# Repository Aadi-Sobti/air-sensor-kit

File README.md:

# ProseFire community air sensor kit

_"ProseFire" is a placeholder name._

A low-cost PM2.5 sensor kit that anyone can build and set up in minutes: a NodeMCU (ESP8266) board plus a
Plantower PMS5003 sensor, a small backend, and a public air-quality map.

## What's where
| Path | What it's for |
|---|---|
| `firmware/` | Sensor firmware (PlatformIO, ESP8266) |
| `backend/` | Firebase functions, database rules, emulator tests |
| `web/` | Website: setup page, owner page, public map |
| `tools/` | Serial log capture, release-build check, (later) device simulator and factory provisioning |
| `docs/PLAN.md` | Milestones and progress |
| `docs/decisions.md` | What's decided and what's still open |
| `docs/USER_FLOW.md` | Exactly what kit recipients and volunteers do |
| `docs/FUTURE.md` | Fire Watch + outage plans (later phases) |
| `docs/reference/` | The original O2NYC workshop deck (old wiring, for reference only) |

## Developer setup (macOS)
```bash
brew install platformio firebase-cli node@22 python@3.12
python3.12 -m venv tools/.venv && tools/.venv/bin/pip install -r tools/requirements.txt
export PATH="$(brew --prefix node@22)/bin:$PATH"   # backend + web use Node 22
```

## Checks (same as CI)
```bash
pio run -d firmware -e release -e dev && pio test -d firmware -e native && python3 tools/check_release.py
tools/.venv/bin/python -m pytest -q tools/tests
(cd backend && npm --prefix functions ci && npm --prefix functions run build && firebase emulators:exec --only functions,firestore "npm --prefix functions test")
(cd web && npm ci && npm test && npm run build)
```

## License
Not chosen yet. Until a license is added, this code is visible but not licensed for reuse.

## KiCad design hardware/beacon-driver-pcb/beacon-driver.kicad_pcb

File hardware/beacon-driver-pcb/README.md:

# Help-First beacon driver board (custom PCB, spin 1)

A 70 × 50 mm, 2-layer board that replaces the hand-soldered 5 × 7 cm "driver board" in the Help-First case
(`hardware/beacon-help-first/`), in the same pocket. **Status: drawn, routed and checked in KiCad 10; not ordered,
not built.** The bench units stay on perfboard with the same circuit (decision #44).

What it does, how and why: [DESIGN.md](DESIGN.md). The decisions behind it: #42–#49 in `docs/decisions.md`.

## Files
| File | What |
|---|---|
| `design.json` | **The source of truth:** every part (KiCad symbol and footprint, LCSC number, value), its pin-to-net map, and its position on the board |
| `build.py` | Turns `design.json` into the KiCad project, routes it, runs KiCad's checks and writes the JLCPCB files and pictures |
| `kigen.py`, `route.py` | Helpers: the label-style schematic writer and a small grid router (pure Python) |
| `beacon-driver.kicad_pro` / `.kicad_sch` / `.kicad_pcb` | The KiCad 10 project (generated: change `design.json` or `build.py`, not these) |
| `beacon-driver.kicad_dru` | JLCPCB-safe design rules (0.2 mm clearance and track, 0.3/0.6 mm vias, 0.5 mm copper to edge) |
| `beacon.pretty/` | Two project footprints: the Pololu U3V40F12 and the Adafruit MAX98357A breakout on their headers, with each module board's outline as the courtyard |
| `beacon-driver-schematic.pdf` | The schematic, for review |
| `beacon-driver-assembly.pdf` | Assembly drawing: every part's reference and outline (for checking JLCPCB's placement preview and naming the test points with no room on the silkscreen) |
| `jlcpcb/beacon-driver-gerbers.zip` | Gerbers + drill files to upload to JLCPCB |
| `jlcpcb/beacon-driver-bom.csv`, `jlcpcb/beacon-driver-cpl.csv` | Parts list and placement file for JLCPCB assembly (48 parts on the top side) |
| `pictures/board-top.png`, `board-bottom.png` | Renders |

## Checks (2026-11-27, KiCad 10.0.8)
- **ERC** (schematic electrical rules): 0 violations.
- **DRC** (layout rules, with schematic parity and zones refilled): 0 errors, 0 warnings, 0 unconnected pads, 0
  schematic-parity issues. Text is at least 1.0 mm high with a 0.16 mm stroke (JLCPCB's minimums).
- **Drill check:** `build.py` confirms all 192 plated holes in the drill file land on a copper pad or via in the
  Gerbers (an earlier version had the drill file on a different origin; the review caught it). Silk near the board edge is the only check turned off: the connectors overhang the right edge
  on purpose, and JLCPCB clips silk there.
- **Fit in the case:** `hardware/beacon-help-first/make_case.py` models the board, its 15 mm part height (13 mm in the
  top 17 mm strip, behind the siren holder), the battery plug and the ribbon socket on the right edge, and passes.
- **Not checked by software:** how the board behaves. That's the bench tests in DESIGN.md, run on the perfboard units
  **before ordering**.

## Rebuilding
KiCad 10.0.x must be available (its normal install needs your Mac password: `brew install --cask kicad`). Then:
```
KICAD_APP=/Applications/KiCad/KiCad.app \
  /Applications/KiCad/KiCad.app/Contents/Frameworks/Python.framework/Versions/Current/bin/python3 \
  hardware/beacon-driver-pcb/build.py
```
It prints the ERC and DRC results and exits non-zero if either finds a problem. To look at or edit the board by hand,
open `beacon-driver.kicad_pro` in KiCad (hand edits are overwritten by the next `build.py` run).

## What you need with this board (per beacon; checked 2026-11-27)
JLCPCB fits all the small parts and the four connectors. Everything else plugs in or solders on by hand. No crimping
tool is needed: the two harnesses come pre-assembled.

| Goes into | What to buy | Price | Per beacon | For 5 | Notes |
|---|---|---|---|---|---|
| **U1** | Pololu [U3V40F12](https://www.pololu.com/product/4016) 12 V booster (#42) | $9.95, $9.15 each for 5 | 1 | 5 | Header strip included. Solder it **flat** on its straight header, parts up, matching the silk (OUT GND GND VIN VIN EN). Pololu showed "backorders allowed" with no count: check stock |
| **U2** | Adafruit [3006](https://www.adafruit.com/product/3006) MAX98357A amplifier | $5.95 | 1 | 5 | Header included; the speaker terminal comes soldered on. Break the header to 7 pins. **Screw the speaker wires in before soldering U2 down** |
| U2's terminal | The speaker you already have (Adafruit [3351](https://www.adafruit.com/product/3351)) | (on the list) | 1 | 5 | Cut off its JST plug (so it can never go into J1 or the LilyGO's SOLAR socket), shorten to about 150 mm, screw in |
| **J1** | The battery (Adafruit [5035](https://www.adafruit.com/product/5035)) plugs straight in | (on the list) | 1 | 5 | Keyed. **First time only:** Hold a bare JST S2B-PH-K-S as it sits on a board (its PCB pins pointing down, the opening facing you), plug the pack in and meter the two pins underneath: the LEFT pin is pin 1 and must read + (3.6–4.2 V). If it reads −, stop and don't plug that pack into a beacon |
| **J2** | 22 AWG stranded wire, red + black: SparkFun [PRT-08865](https://www.sparkfun.com/products/8865) and [PRT-08867](https://www.sparkfun.com/products/8867) (25 ft each) | $5.95 each | ≈ 150 mm each | 1 spool each | Red from J2 "+" to the LilyGO 18650 holder's + tab (ESP32 end), black from "−" to its − tab (antenna end). Solder the holder end before the LilyGO goes on its posts |
| **J3** | A 14-pin (2 × 7) IDC ribbon cable, cut in half: 3M [M3AAA-1418J](https://www.digikey.com/en/products/detail/3m/M3AAA-1418J/229962), 1.5 ft | ≈ $5.60–6.38 (not confirmed) | ½ cable | 3 cables | **DigiKey stock not confirmed** (it blocked the check): look in a browser. Each half is about 220 mm. Peel the cut end once, between wires 7 and 8: wires 1–7 go to LilyGO row P1, 8–14 to row P2 (table in DESIGN.md). Hot-glue the ribbon near the LilyGO so the solder joints don't flex. **If it's out of stock:** 3M 89114-0001 IDC sockets (Master Electronics, $1.19 each, minimum 25) on 14-way 1.27 mm ribbon, pressed shut in a bench vise |
| **J4** | Adafruit [4876](https://www.adafruit.com/product/4876) 6-pin JST-XH-compatible cable pair | $1.25 | 1 (socket half) | 5 | Pre-crimped, 26 AWG, about 20 cm. Tag each wire with its pin number. Solder the far ends: 1–2 siren +/−, 3–4 light strip +/−, 5–6 red-button light +/− |
| **J5** | Adafruit [5090](https://www.adafruit.com/product/5090) 6-pin JST-PH-compatible cable pair | $0.95 | 1 (socket half) | 5 | Pre-crimped, 26 AWG. Pin 1 GND (daisy-chain to the green LED −, green switch, red switch and silence button with short black jumpers), 2 green LED +, 3 green switch, 4 red switch, 5 silence button; cut pin 6 short and insulate it |
| J5 pin 5 | Adafruit [1502](https://www.adafruit.com/product/1502) 16 mm yellow push button: the **SILENCE** button (#48) | $0.95 | 1 | 5 (+1 spare) | Normally open. Mounts on top of the case. Solder two wires: one to J5 pin 5, one to GND |
| **J6** | 26 AWG silicone wire, gray (tip) + black (sleeve): Adafruit [1884](https://www.adafruit.com/product/1884) and [1881](https://www.adafruit.com/product/1881), 2 m each | $0.95 each | ≈ 200 mm each | 1 gray + 2 black | Gray from "TIP" to the jack's tip lug, black from "SLV" to its sleeve lug. The extra black is for the J5 ground jumpers. Measure the shaker's plug first: it must be tip-positive (#47) |
| Under the board | Foam tape **no thicker than 1 mm** (Adafruit [5019](https://www.adafruit.com/product/5019) says both "1mm" and 0.063 in, so measure it) | $0.75 | 2 strips | 4 packs | Cut strips about 1.5 mm wide for the two ledges. Thicker tape pushes the board into the siren holder's space |
| Building | Lead-free solder (SparkFun [TOL-09163](https://www.sparkfun.com/products/9163)), heat-shrink (Adafruit [1649](https://www.adafruit.com/product/1649)), a flux pen and desoldering braid | $4.95 each | | | Tools: soldering iron, flush cutters (trim every lead under the board to 2 mm or less), wire stripper, multimeter, small screwdriver, heat gun |

**Add-on cost per beacon:** about $22 (the two modules $15.10, cables and wire about $5, the silence button $0.95),
plus the board itself. The modules and speaker are needed on perfboard too.

## Ordering from JLCPCB (founder steps; nothing has been ordered)
1. **Before ordering:** the perfboard bench units pass the bench tests in DESIGN.md, and an experienced engineer has
   looked over the schematic PDF and the board (`docs/BEACON_PCB.md` step 6).
2. **Account:** JLCPCB needs an account. Under 18, its terms need a parent's or guardian's permission, or an adult
   officer of the nonprofit can order. Payment is yours.
3. **Board:** upload `jlcpcb/beacon-driver-gerbers.zip`. Settings: 2 layers, 70 × 50 mm, 1.6 mm, 1 oz copper,
   lead-free HASL, quantity 5.
4. **Assembly:** turn on PCB Assembly, **Economic**, top side, 5 boards. Upload `beacon-driver-bom.csv` and
   `beacon-driver-cpl.csv`. Tick **"Confirm parts placement"**.
5. **Check the placement preview** against `beacon-driver-assembly.pdf`. KiCad and JLCPCB sometimes disagree on a
   part's rotation; fix any that look turned in JLCPCB's own tool. What correct looks like (board seen from the top,
   battery socket at the bottom right):
   - **C1** (the round can): + on the LEFT, the dark stripe (−) on the RIGHT.
   - **D2 and TVS1:** cathode band on the LEFT. **D1:** cathode band on the RIGHT.
   - **Q11** (square, bottom right): its 4 small pins on the LEFT, the big tab on the RIGHT toward R1.
   - **Q16** (square, left): small pins on the RIGHT, big tab on the LEFT toward F1.
   - **Q12, Q13, Q15** (top row): the single pin points DOWN toward the white J4 connector. **Q14:** single pin RIGHT.
   - **J1, J3, J4 and J5 are listed at their pin 1, not their middle,** so the preview may draw them shifted by up to
     about 9 mm: drag each one onto its holes.
   - **J1** opening facing the RIGHT edge; **J3**'s shroud at the right edge, opening facing right; **J4/J5** with pin 1
     at the LEFT end, as on the assembly drawing.
6. **Parts JLCPCB doesn't fit:** U1 (Pololu U3V40F12), U2 (Adafruit 3006), the J2 and J6 wires, and the cables. See the
   list below.
7. **Checkout:** choose DDP, so the US import duty (about 35%) is paid up front.

Cost estimate (not a quote): about $64 for 5 assembled boards before duty and shipping, about $100–117 delivered; see
DESIGN.md.

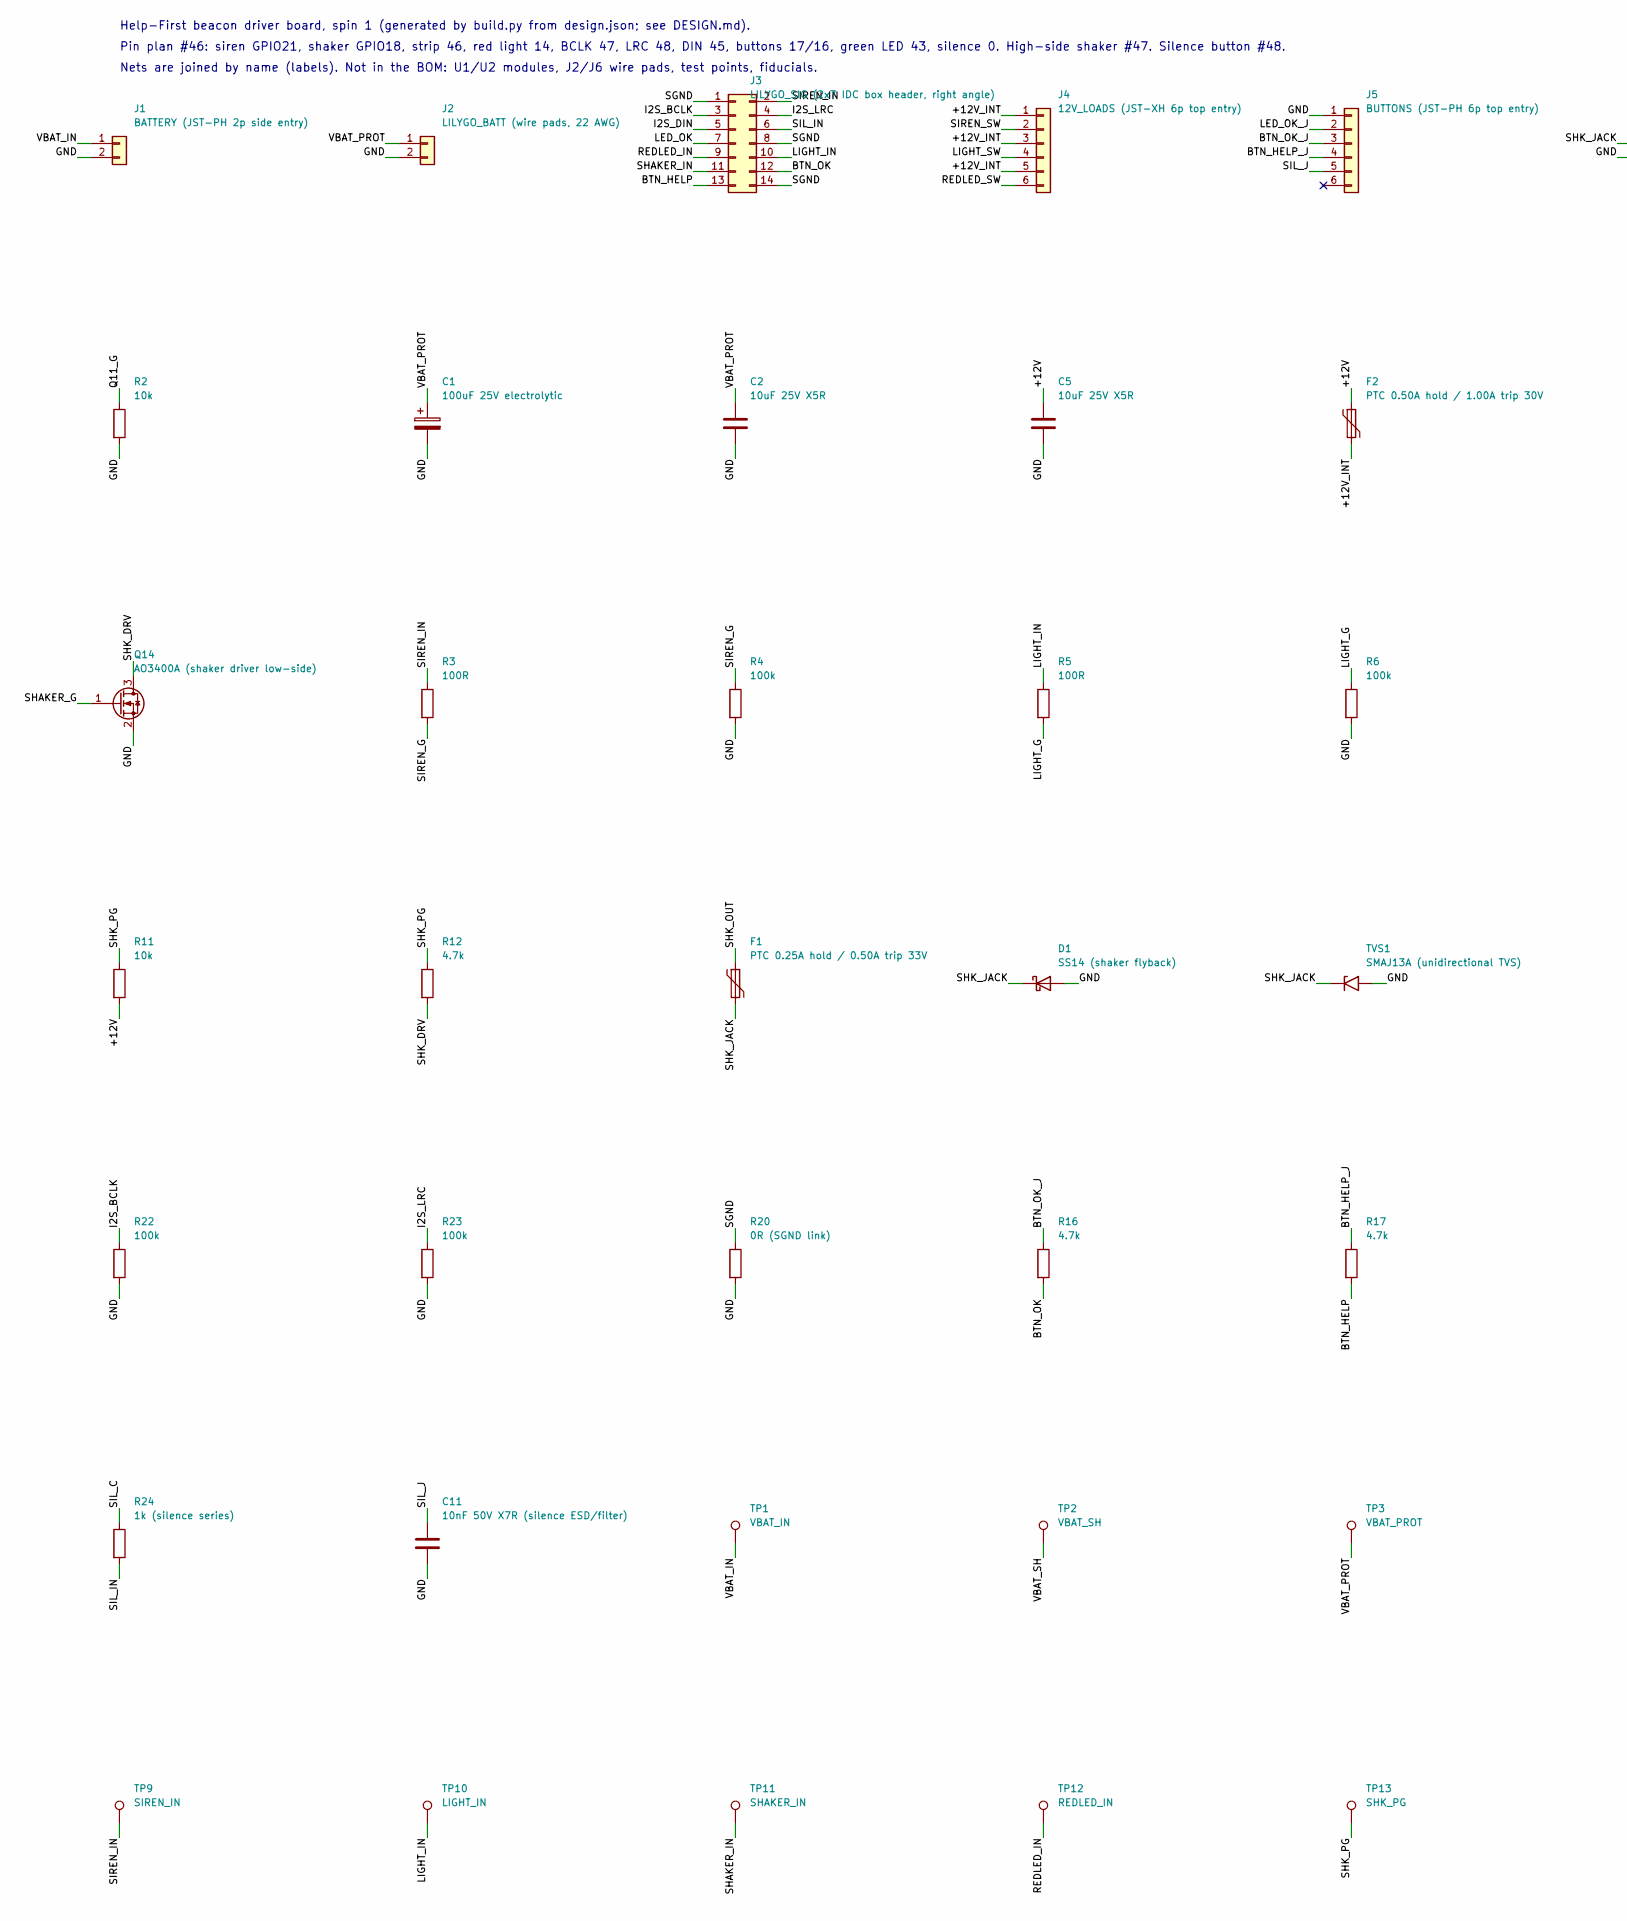
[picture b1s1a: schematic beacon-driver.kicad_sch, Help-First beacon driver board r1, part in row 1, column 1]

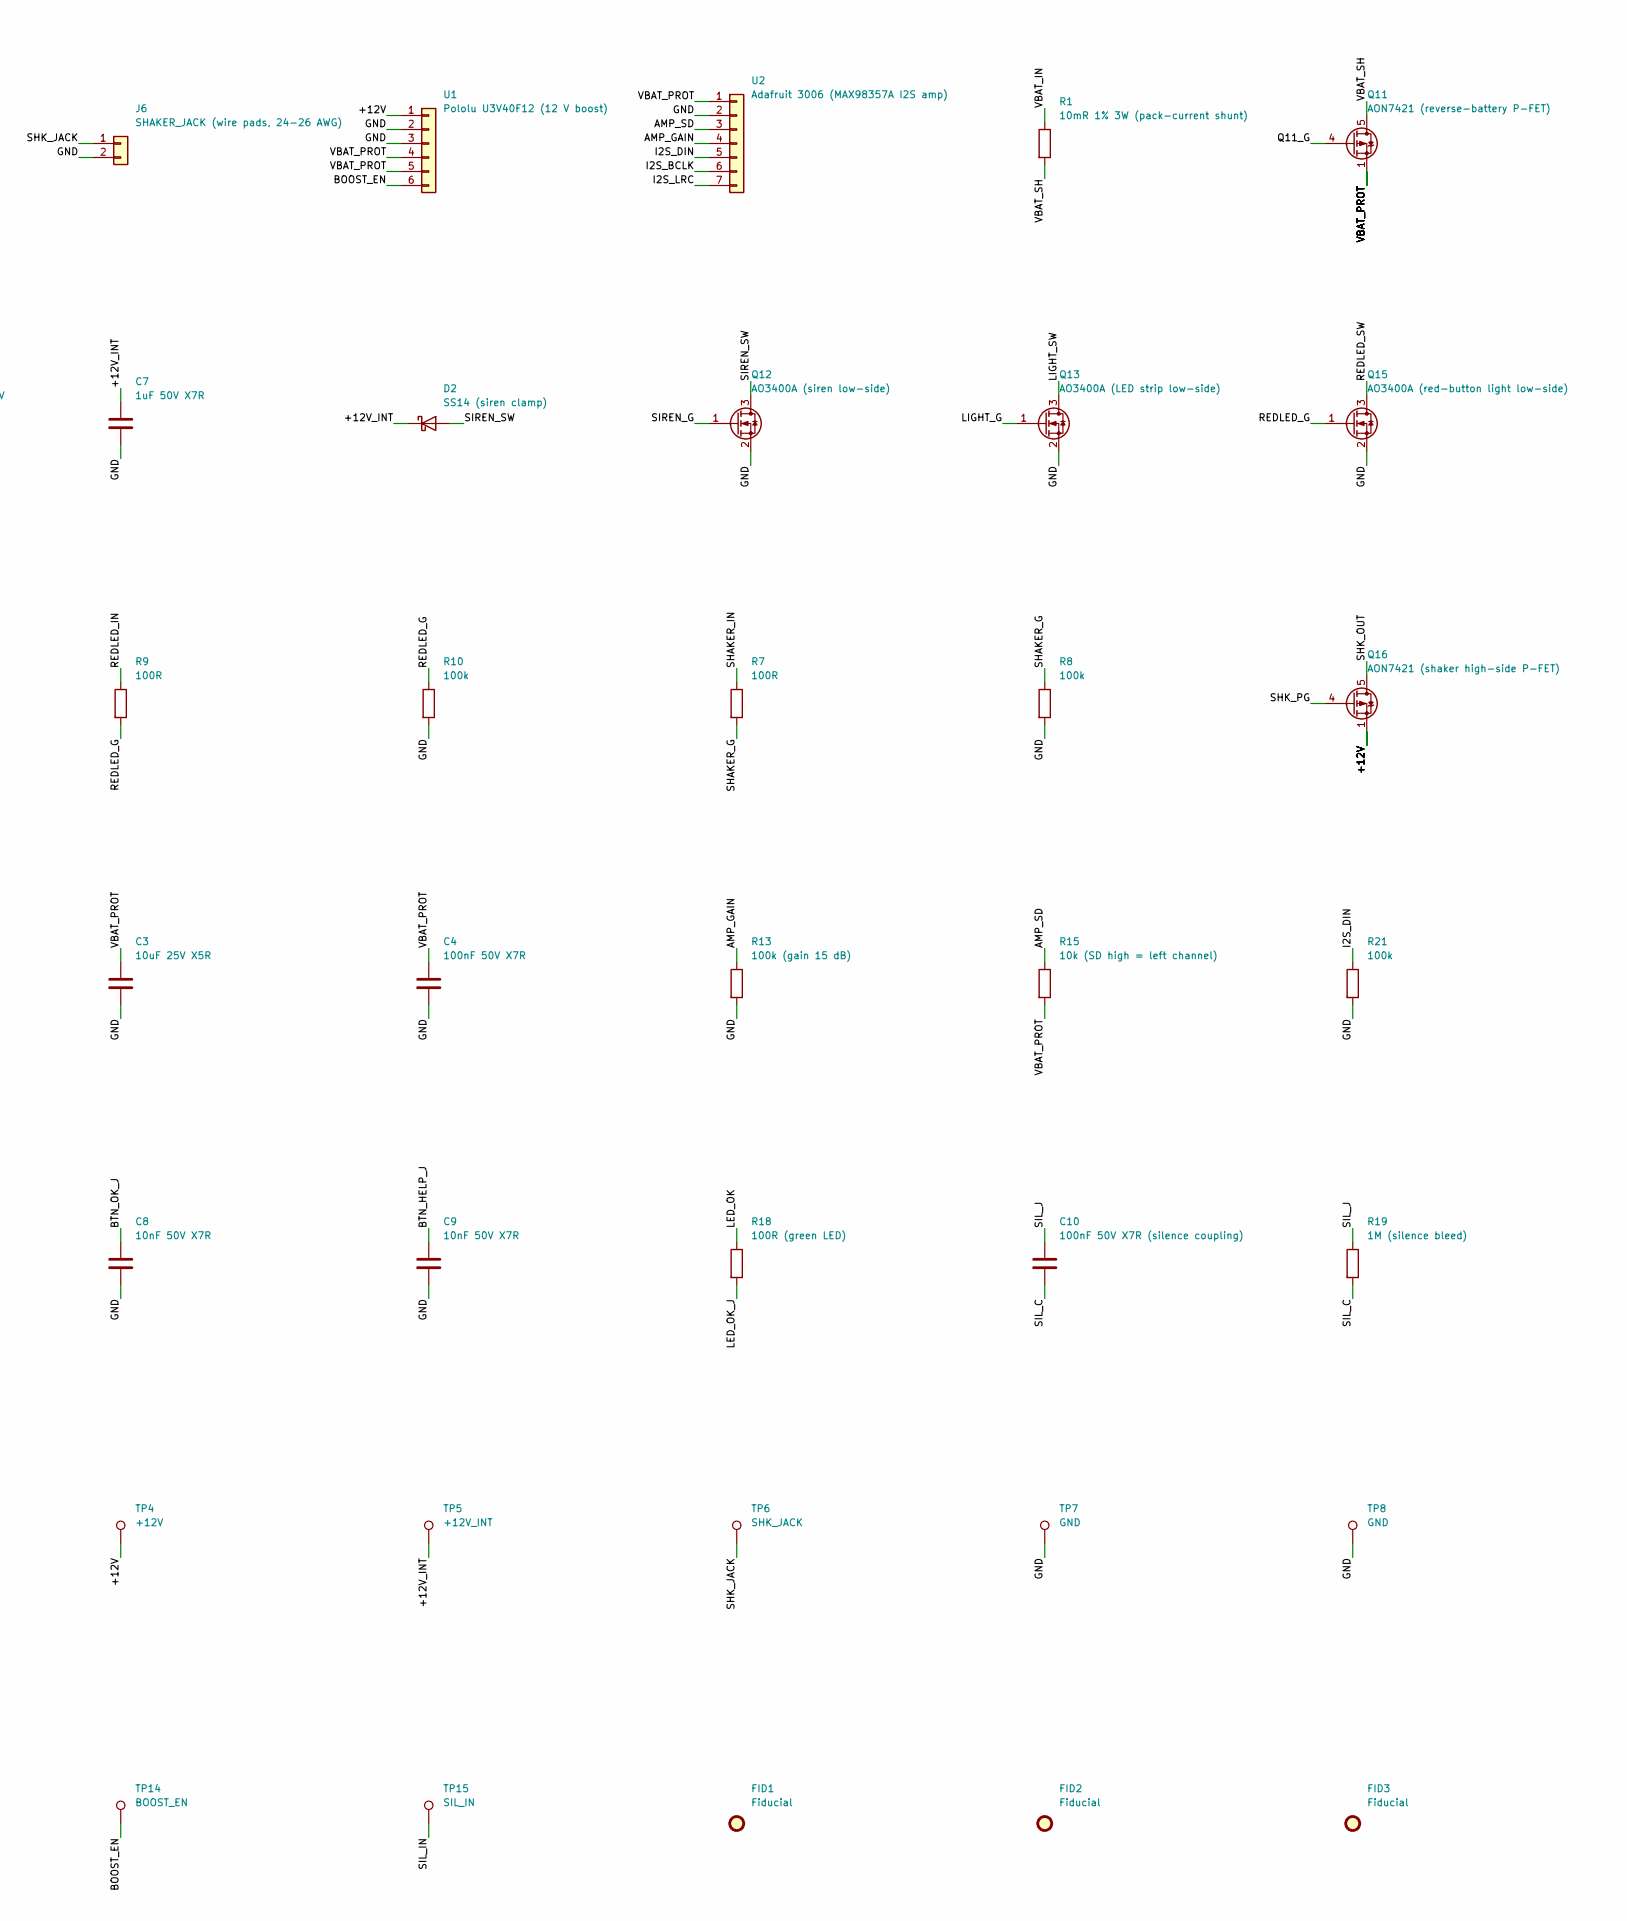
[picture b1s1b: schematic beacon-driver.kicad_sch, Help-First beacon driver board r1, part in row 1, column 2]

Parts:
C1: 100uF 25V electrolytic; CP_Elec_6.3x7.7; MPN ROQANG RVT1E101M0607; LCSC C72477
C2, C3, C5: 10uF 25V X5R; C_0805_2012Metric; MPN Samsung CL21A106KAYNNNE; LCSC C15850
C4: 100nF 50V X7R; C_0603_1608Metric; MPN YAGEO CC0603KRX7R9BB104; LCSC C14663
C7: 1uF 50V X7R; C_0805_2012Metric; MPN Samsung CL21B105KBFNNNE; LCSC C28323
C8, C9: 10nF 50V X7R; C_0603_1608Metric; MPN FH 0603B103K500NT; LCSC C57112
C10: 100nF 50V X7R (silence coupling); C_0603_1608Metric; MPN YAGEO CC0603KRX7R9BB104; LCSC C14663
C11: 10nF 50V X7R (silence ESD/filter); C_0603_1608Metric; MPN FH 0603B103K500NT; LCSC C57112
D1: SS14 (shaker flyback); D_SMA; MPN MDD SS14; LCSC C2480
D2: SS14 (siren clamp); D_SMA; MPN MDD SS14; LCSC C2480
F1: PTC 0.25A hold / 0.50A trip 33V; Fuse_1206_3216Metric; MPN BHFUSE BSMD1206-025-33V; LCSC C2977524
F2: PTC 0.50A hold / 1.00A trip 30V; Fuse_1206_3216Metric; MPN BHFUSE BSMD1206-050-30V; LCSC C883126
FID1, FID2, FID3: Fiducial; Fiducial_1mm_Mask2mm; MPN none (copper dot)
J1: BATTERY (JST-PH 2p side entry); JST_PH_S2B-PH-K_1x02_P2.00mm_Horizontal; MPN JST S2B-PH-K-S(LF)(SN); LCSC C173752
J2: LILYGO_BATT (wire pads, 22 AWG); SolderWire-0.5sqmm_1x02_P4.6mm_D0.9mm_OD2.1mm; MPN none (wire)
J3: LILYGO_SIG (2x7 IDC box header, right angle); IDC-Header_2x07_P2.54mm_Horizontal; MPN HCTL HC-JN254-2-07-W; LCSC C5372874
J4: 12V_LOADS (JST-XH 6p top entry); JST_XH_B6B-XH-A_1x06_P2.50mm_Vertical; MPN JST B6B-XH-A(LF)(SN); LCSC C144397
J5: BUTTONS (JST-PH 6p top entry); JST_PH_B6B-PH-K_1x06_P2.00mm_Vertical; MPN JST B6B-PH-K-S(LF)(SN); LCSC C131342
J6: SHAKER_JACK (wire pads, 24-26 AWG); SolderWire-0.25sqmm_1x02_P4.2mm_D0.65mm_OD1.7mm; MPN none (wire)
Q11: AON7421 (reverse-battery P-FET); Vishay_PowerPAK_1212-8_Single; MPN AOS AON7421; LCSC C115842
Q12: AO3400A (siren low-side); SOT-23; MPN AOS AO3400A; LCSC C20917
Q13: AO3400A (LED strip low-side); SOT-23; MPN AOS AO3400A; LCSC C20917
Q14: AO3400A (shaker driver low-side); SOT-23; MPN AOS AO3400A; LCSC C20917
Q15: AO3400A (red-button light low-side); SOT-23; MPN AOS AO3400A; LCSC C20917
Q16: AON7421 (shaker high-side P-FET); Vishay_PowerPAK_1212-8_Single; MPN AOS AON7421; LCSC C115842
R1: 10mR 1% 3W (pack-current shunt); R_2512_6332Metric; MPN Milliohm HoYLR2512-3W-10mR-1%; LCSC C5375464
R2, R11: 10k; R_0603_1608Metric; MPN UNI-ROYAL 0603WAF1002T5E; LCSC C25804
R3, R5, R7, R9: 100R; R_0603_1608Metric; MPN UNI-ROYAL 0603WAF1000T5E; LCSC C22775
R4, R6, R8, R10, R21, R22, R23: 100k; R_0603_1608Metric; MPN UNI-ROYAL 0603WAF1003T5E; LCSC C25803
R12, R16, R17: 4.7k; R_0603_1608Metric; MPN UNI-ROYAL 0603WAF4701T5E; LCSC C23162
R13: 100k (gain 15 dB); R_0603_1608Metric; MPN UNI-ROYAL 0603WAF1003T5E; LCSC C25803
R15: 10k (SD high = left channel); R_0603_1608Metric; MPN UNI-ROYAL 0603WAF1002T5E; LCSC C25804
R18: 100R (green LED); R_0603_1608Metric; MPN UNI-ROYAL 0603WAF1000T5E; LCSC C22775
R19: 1M (silence bleed); R_0603_1608Metric; MPN UNI-ROYAL 0603WAF1004T5E; LCSC C22935
R20: 0R (SGND link); R_1206_3216Metric; MPN UNI-ROYAL 1206W4F0000T5E; LCSC C17888
R24: 1k (silence series); R_0603_1608Metric; MPN UNI-ROYAL 0603WAF1001T5E; LCSC C21190
TP1: VBAT_IN; TestPoint_Pad_D1.5mm; MPN none (bare 1.5 mm pad)
TP2: VBAT_SH; TestPoint_Pad_D1.5mm; MPN none (bare 1.5 mm pad)
TP3: VBAT_PROT; TestPoint_Pad_D1.5mm; MPN none (bare 1.5 mm pad)
TP4: +12V; TestPoint_Pad_D1.5mm; MPN none (bare 1.5 mm pad)
TP5: +12V_INT; TestPoint_Pad_D1.5mm; MPN none (bare 1.5 mm pad)
TP6: SHK_JACK; TestPoint_Pad_D1.5mm; MPN none (bare 1.5 mm pad)
TP7, TP8: GND; TestPoint_Pad_D1.5mm; MPN none (bare 1.5 mm pad)
TP9: SIREN_IN; TestPoint_Pad_D1.5mm; MPN none (bare 1.5 mm pad)
TP10: LIGHT_IN; TestPoint_Pad_D1.5mm; MPN none (bare 1.5 mm pad)
TP11: SHAKER_IN; TestPoint_Pad_D1.5mm; MPN none (bare 1.5 mm pad)
TP12: REDLED_IN; TestPoint_Pad_D1.5mm; MPN none (bare 1.5 mm pad)
TP13: SHK_PG; TestPoint_Pad_D1.5mm; MPN none (bare 1.5 mm pad)
TP14: BOOST_EN; TestPoint_Pad_D1.5mm; MPN none (bare 1.5 mm pad)
TP15: SIL_IN; TestPoint_Pad_D1.5mm; MPN none (bare 1.5 mm pad)
TVS1: SMAJ13A (unidirectional TVS); D_SMA; MPN MDD SMAJ13A (alt. Littelfuse SMAJ13A, C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; LCSC C153724
U1: Pololu U3V40F12 (12 V boost); Pololu_U3V40F12_Flat; MPN Pololu U3V40F12
U2: Adafruit 3006 (MAX98357A I2S amp); Adafruit_3006_MAX98357A; MPN Adafruit 3006

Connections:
/+12V: C5.1, F2.1, Q16.1 (S), Q16.2 (S), Q16.3 (S), R11.2, TP4.1, U1.1
/+12V_INT: C7.1, D2.1 (K), F2.2, J4.1, J4.3, J4.5, TP5.1
/AMP_GAIN: R13.1, U2.4
/AMP_SD: R15.1, U2.3
/BOOST_EN: TP14.1, U1.6
/BTN_HELP: J3.13, R17.2
/BTN_HELP_J: C9.1, J5.4, R17.1
/BTN_OK: J3.12, R16.2
/BTN_OK_J: C8.1, J5.3, R16.1
/GND: C1.2, C2.2, C3.2, C4.2, C5.2, C7.2, C8.2, C9.2, C11.2, D1.2 (A), J1.2, J2.2, J5.1, J6.2, Q12.2 (S), Q13.2 (S), Q14.2 (S), Q15.2 (S), R2.2, R4.2, R6.2, R8.2, R10.2, R13.2, R20.2, R21.2, R22.2, R23.2, TP7.1, TP8.1, TVS1.2 (A2), U1.2, U1.3, U2.2
/I2S_BCLK: J3.3, R22.1, U2.6
/I2S_DIN: J3.5, R21.1, U2.5
/I2S_LRC: J3.4, R23.1, U2.7
/LED_OK: J3.7, R18.1
/LED_OK_J: J5.2, R18.2
/LIGHT_G: Q13.1 (G), R5.2, R6.1
/LIGHT_IN: J3.10, R5.1, TP10.1
/LIGHT_SW: J4.4, Q13.3 (D)
/Q11_G: Q11.4 (G), R2.1
/REDLED_G: Q15.1 (G), R9.2, R10.1
/REDLED_IN: J3.9, R9.1, TP12.1
/REDLED_SW: J4.6, Q15.3 (D)
/SGND: J3.1, J3.8, J3.14, R20.1
/SHAKER_G: Q14.1 (G), R7.2, R8.1
/SHAKER_IN: J3.11, R7.1, TP11.1
/SHK_DRV: Q14.3 (D), R12.2
/SHK_JACK: D1.1 (K), F1.2, J6.1, TP6.1, TVS1.1 (A1)
/SHK_OUT: F1.1, Q16.5 (D)
/SHK_PG: Q16.4 (G), R11.1, R12.1, TP13.1
/SIL_C: C10.2, R19.2, R24.1
/SIL_IN: J3.6, R24.2, TP15.1
/SIL_J: C10.1, C11.1, J5.5, R19.1
/SIREN_G: Q12.1 (G), R3.2, R4.1
/SIREN_IN: J3.2, R3.1, TP9.1
/SIREN_SW: D2.2 (A), J4.2, Q12.3 (D)
/VBAT_IN: J1.1, R1.1, TP1.1
/VBAT_PROT: C1.1, C2.1, C3.1, C4.1, J2.1, Q11.1 (S), Q11.2 (S), Q11.3 (S), R15.2, TP3.1, U1.4, U1.5, U2.1
/VBAT_SH: Q11.5 (D), R1.2, TP2.1

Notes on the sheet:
Pin plan #46: siren GPIO21, shaker GPIO18, strip 46, red light 14, BCLK 47, LRC 48, DIN 45, buttons 17/16, green LED 43, silence 0. High-side shaker #47. Silence button #48.
Help-First beacon driver board, spin 1 (generated by build.py from design.json; see DESIGN.md).
Nets are joined by name (labels). Not in the BOM: U1/U2 modules, J2/J6 wire pads, test points, fiducials.

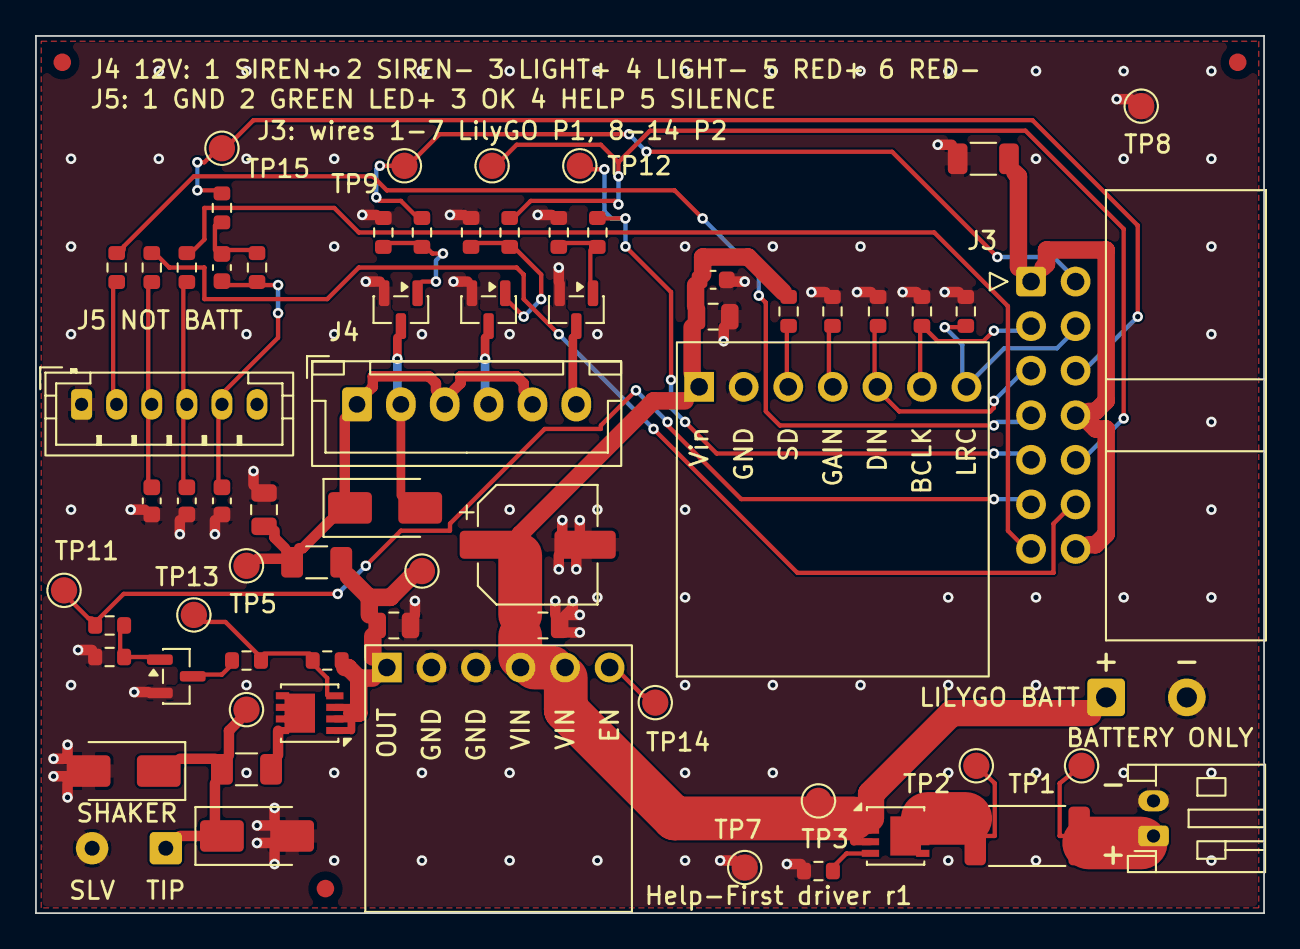
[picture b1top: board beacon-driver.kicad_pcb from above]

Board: 2 copper layers, 70.0 x 50.0 mm, 70 parts (0 on the bottom side), 38 nets.

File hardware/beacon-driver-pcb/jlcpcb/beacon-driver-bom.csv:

Comment,Designator,Footprint,LCSC Part #
100uF 25V electrolytic,C1,CP_Elec_6.3x7.7,C72477
10uF 25V X5R,"C2,C3,C5",C_0805_2012Metric,C15850
100nF 50V X7R,"C4,C10",C_0603_1608Metric,C14663
1uF 50V X7R,C7,C_0805_2012Metric,C28323
10nF 50V X7R,"C8,C9,C11",C_0603_1608Metric,C57112
SS14,"D1,D2",D_SMA,C2480
PTC 0.25A hold / 0.50A trip 33V,F1,Fuse_1206_3216Metric,C2977524
PTC 0.50A hold / 1.00A trip 30V,F2,Fuse_1206_3216Metric,C883126
BATTERY,J1,JST_PH_S2B-PH-K_1x02_P2.00mm_Horizontal,C173752
LILYGO_SIG,J3,IDC-Header_2x07_P2.54mm_Horizontal,C5372874
12V_LOADS,J4,JST_XH_B6B-XH-A_1x06_P2.50mm_Vertical,C144397
BUTTONS,J5,JST_PH_B6B-PH-K_1x06_P2.00mm_Vertical,C131342
AON7421,"Q11,Q16",Vishay_PowerPAK_1212-8_Single,C115842
AO3400A,"Q12,Q13,Q14,Q15",SOT-23,C20917
10mR 1% 3W,R1,R_2512_6332Metric,C5375464
10k,"R2,R11,R15",R_0603_1608Metric,C25804
100R,"R3,R5,R7,R9,R18",R_0603_1608Metric,C22775
100k,"R4,R6,R8,R10,R13,R21,R22,R23",R_0603_1608Metric,C25803
4.7k,"R12,R16,R17",R_0603_1608Metric,C23162
1M,R19,R_0603_1608Metric,C22935
0R,R20,R_1206_3216Metric,C17888
1k,R24,R_0603_1608Metric,C21190
SMAJ13A,TVS1,D_SMA,C153724
